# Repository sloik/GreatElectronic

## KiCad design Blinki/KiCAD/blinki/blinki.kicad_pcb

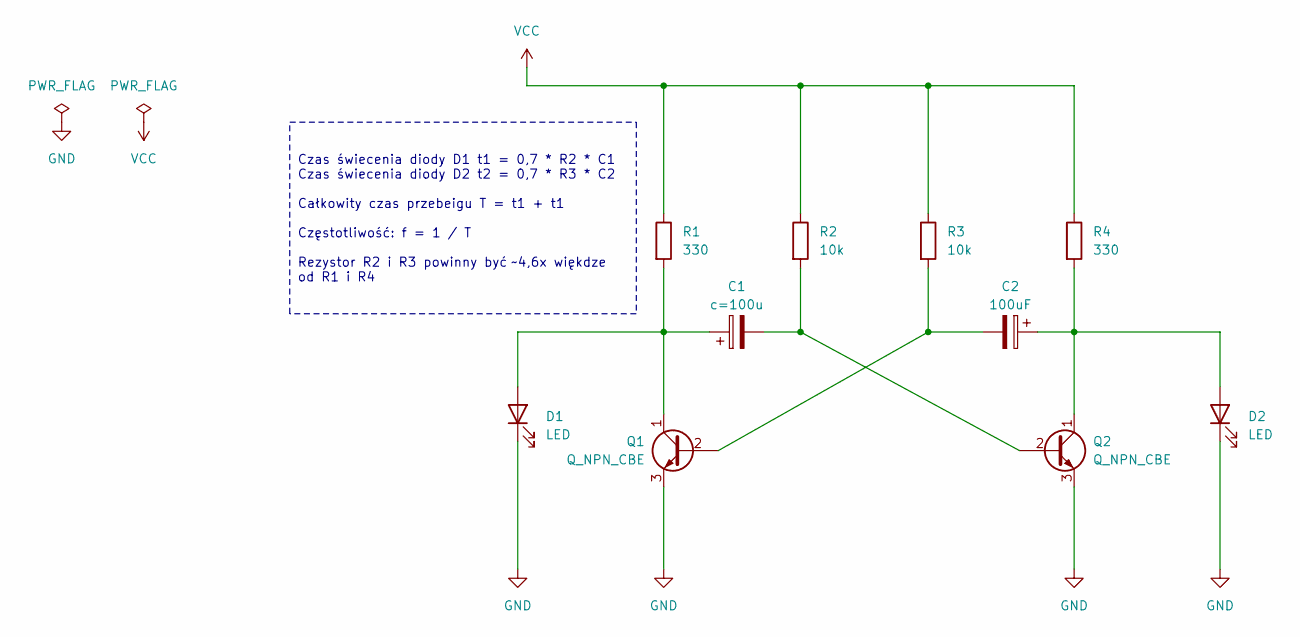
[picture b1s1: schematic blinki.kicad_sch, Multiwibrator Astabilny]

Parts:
C1: c=100u; CP_Radial_D8.0mm_P5.00mm
C2: 100uF; CP_Radial_D8.0mm_P5.00mm
D1, D2: LED; LED_D5.0mm
Q1, Q2: Q_NPN_CBE; TO-92_Inline_Wide
R1, R4: 330; R_Axial_DIN0204_L3.6mm_D1.6mm_P1.90mm_Vertical
R2, R3: 10k; R_Axial_DIN0204_L3.6mm_D1.6mm_P1.90mm_Vertical

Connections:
GND: D1.1 (K), D2.1 (K), Q1.3 (E), Q2.3 (E)
unnamed: C1.1, D1.2 (A), Q1.1 (C), R1.2
unnamed: C2.1, D2.2 (A), Q2.1 (C), R4.2
unnamed: C2.2, Q1.2 (B), R3.2
unnamed: C1.2, Q2.2 (B), R2.2
VCC: R1.1, R2.1, R3.1, R4.1

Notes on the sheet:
Czas świecenia diody D1 t1 = 0,7 * R2 * C1 Czas świecenia diody D2 t2 = 0,7 * R3 * C2 Całkowity czas przebeigu T = t1 + t1 Częstotliwość: f = 1 / T Rezystor R2 i R3 powinny być ~4,6x więkdze od R1 i R4

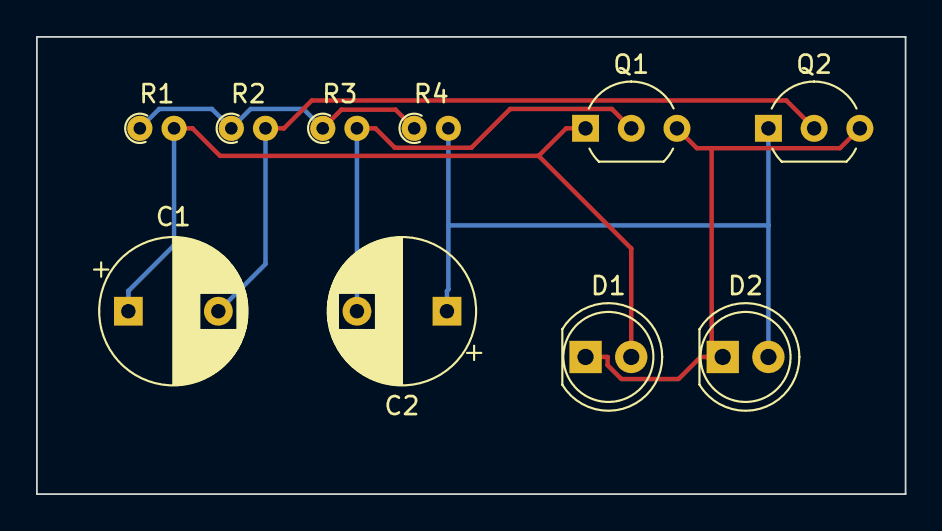
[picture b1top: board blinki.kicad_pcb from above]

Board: 2 copper layers, 48.3 x 25.4 mm, 10 parts (0 on the bottom side), 6 nets.

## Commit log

2023-08-06 Adds blinki schematic and connection documentation.
2023-08-06 Fixes ERC errors by adding power flags.
2023-08-06 Nicer diagram.
2023-08-06 Adds info for simulation.
2023-08-06 Adds layout.
2023-08-06 Stop tracking file.
